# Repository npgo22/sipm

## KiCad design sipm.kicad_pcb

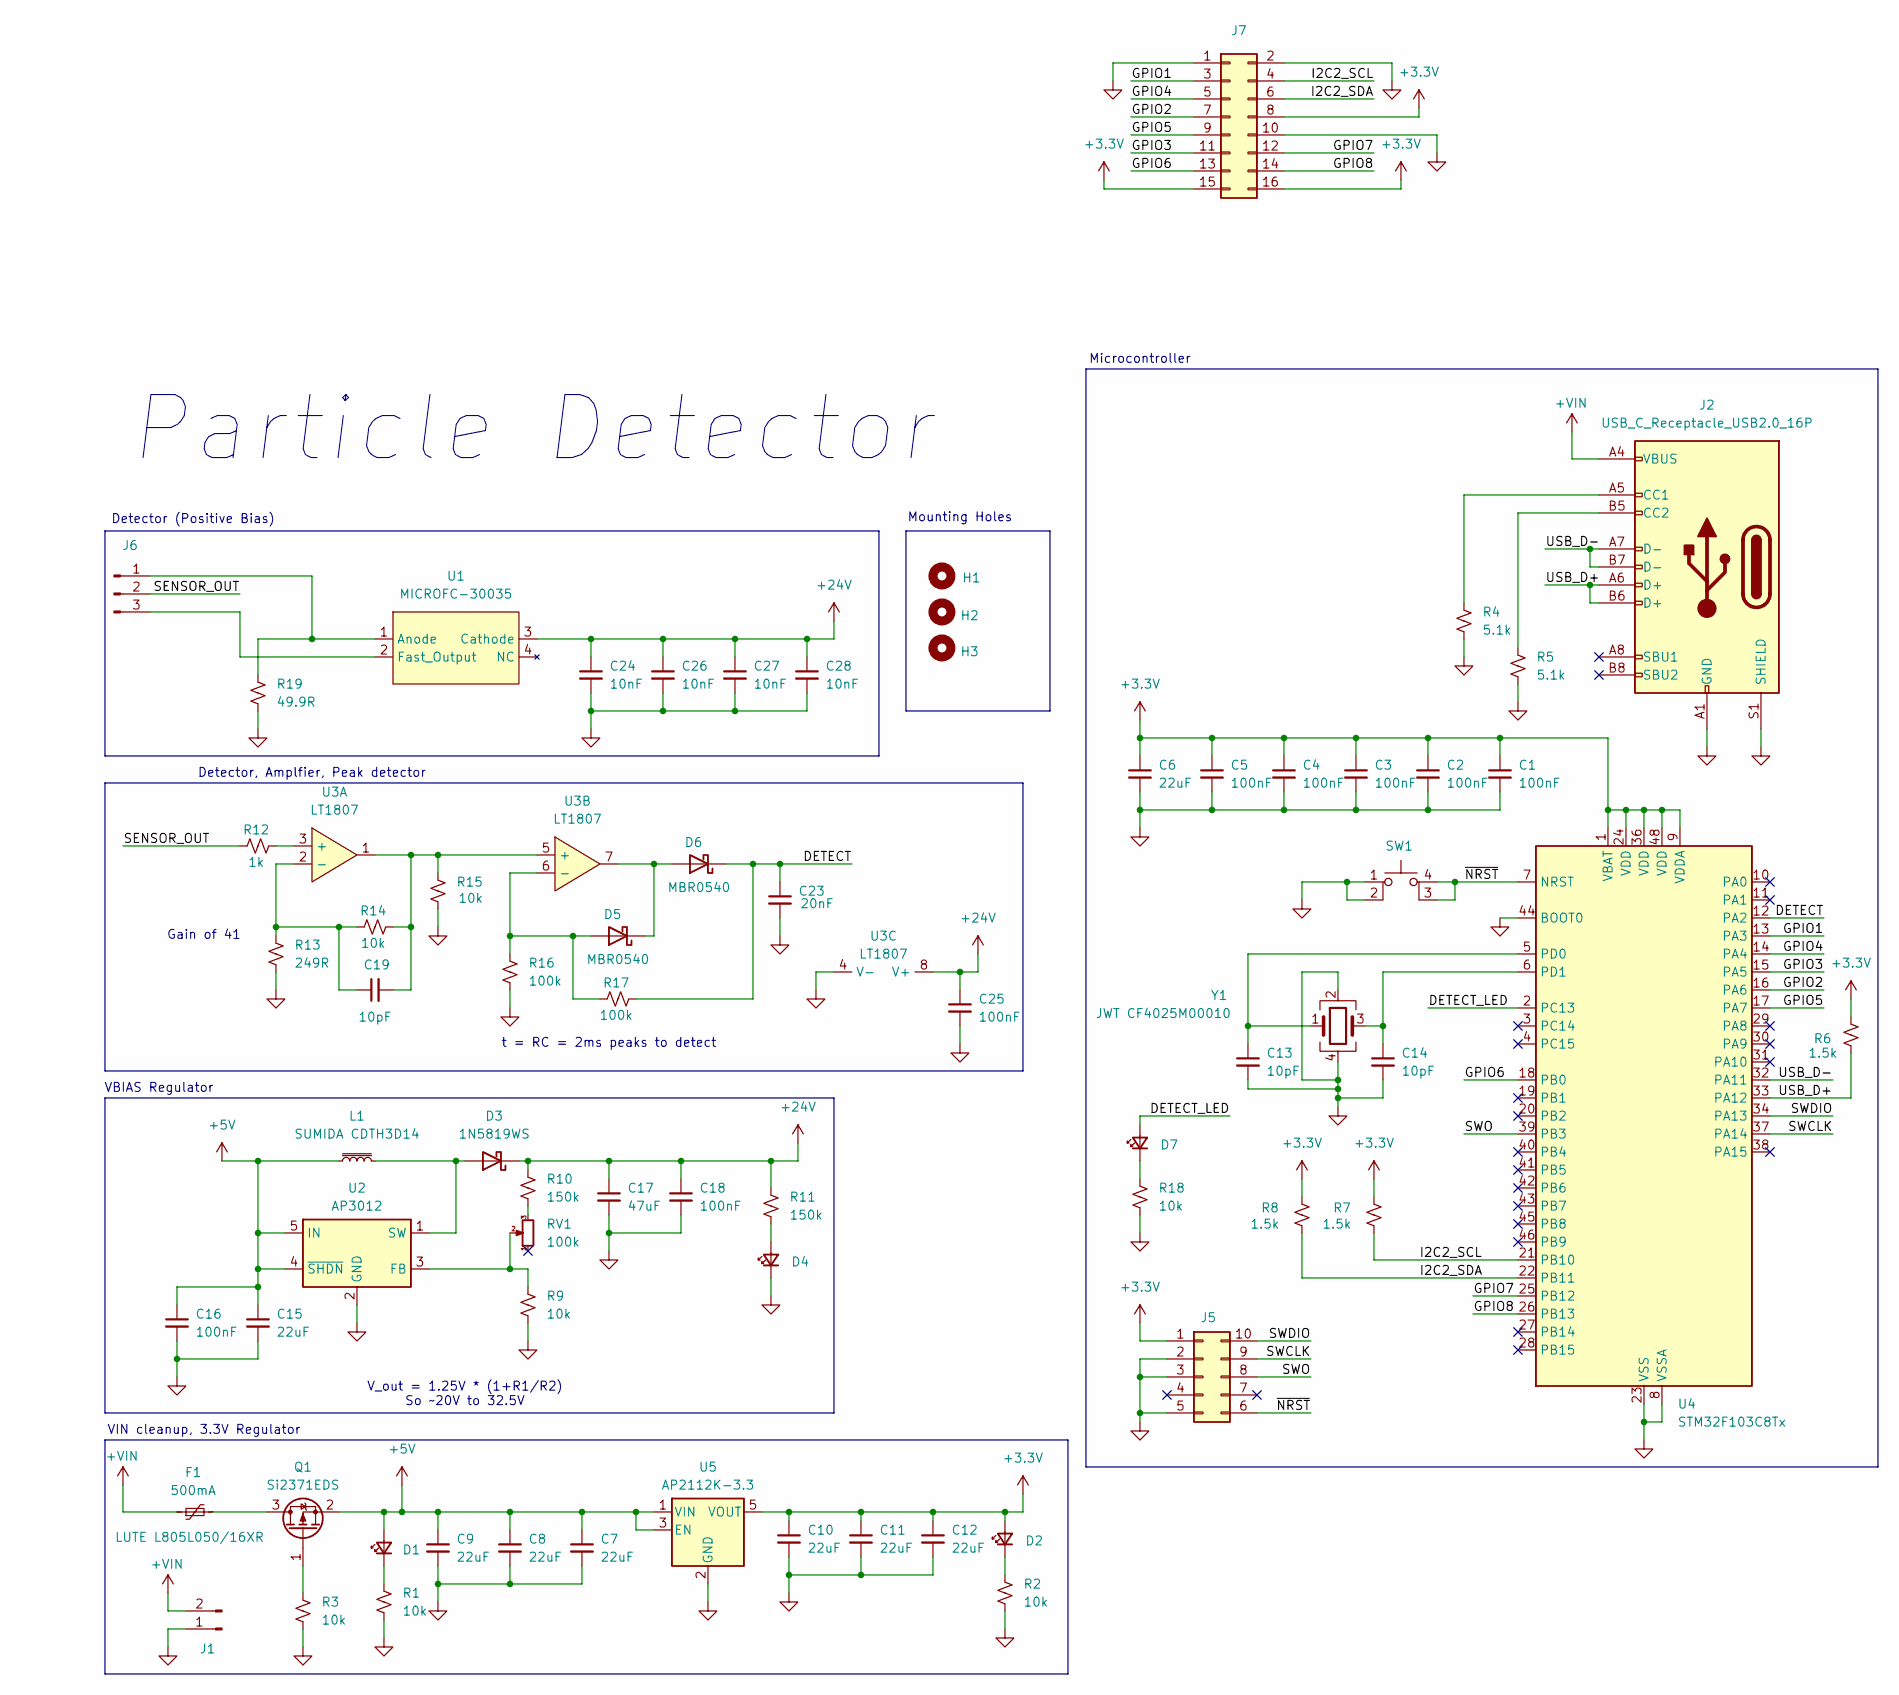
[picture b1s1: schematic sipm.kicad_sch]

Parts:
C1, C2, C3, C4, C5, C16, C18, C25: 100nF; C_0603
C6, C7, C8, C9, C10, C11, C12, C15: 22uF; C_0805
C13, C14, C19: 10pF; C_0603
C17: 47uF; CP_Elec_6.3x5.7
C23: 20nF; C_0603
C24, C26, C27, C28: 10nF; C_0603
D1, D2, D4, D7: LED_Small; LED_0603
D3: 1N5819WS; D_SOD-123F
D5, D6: MBR0540; D_SOD-123
F1: 500mA; F0805
H1, H2, H3: MountingHole; MountingHole_2.2mm_M2
J1: Conn_01x02_Pin; PinHeader_1x02_P2.54mm_Vertical_SMD_Pin1Right
J2: USB_C_Receptacle_USB2.0_16P; USB_C_Receptacle_HRO_TYPE-C-31-M-12
J5: Conn_02x05_Counter_Clockwise; PinHeader_2x05_P2.54mm_Vertical_SMD
J6: Conn_01x03_Pin; PinHeader_1x03_P2.54mm_Vertical_SMD_Pin1Right
J7: Conn_02x08_Top_Bottom; PinHeader_2x08_P2.54mm_Vertical_SMD
L1: SUMIDA CDTH3D14
Q1: Si2371EDS; SOT-23
R1, R2, R3, R9, R14, R15, R18: 10k; R_0603
R4, R5: 5.1k; R_0603
R6, R7, R8: 1.5k; R_0603
R10, R11: 150k; R_0603
R12: 1k; R_0603
R13: 249R; R_0603
R16, R17: 100k; R_0603
R19: 49.9R; R_0603
RV1: 100k; Potentiometer_Vishay_TS53YL_Vertical
SW1: SW_MEC_5E; SKRPANE010
U1: MICROFC-30035; XDCR_MICROFC-30035-SMT-TR1
U2: AP3012; SOT-23-5
U3: LT1807; SOIC-8
U4: STM32F103C8Tx; LQFP-48_7x7mm_P0.5mm
U5: AP2112K-3.3; SOT-23-5
Y1: JWT CF4025M00010; 3225-4P

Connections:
+3.3V: C1.1, C2.1, C3.1, C4.1, C5.1, C6.1, C10.1, C11.1, C12.1, D2.2 (A), J5.1, J7.8, J7.15, J7.16, R6.2, R7.2, R8.2, U4.1 (VBAT), U4.9 (VDDA), U4.24 (VDD), U4.36 (VDD), U4.48 (VDD), U5.5 (VOUT)
+5V: C7.1, C8.1, C9.1, C15.1, C16.1, D1.2 (A), L1.1, Q1.2 (S), U2.4 (~SHDN), U2.5 (IN), U5.1 (VIN), U5.3 (EN)
+24V: C17.1, C18.1, C24.1, C25.1, C26.1, C27.1, C28.1, D3.1 (K), R10.1, R11.1, U1.3 (Cathode), U3.8 (V+)
+VIN: F1.1, J1.2, J2.A4 (VBUS), J2.A9 (VBUS), J2.B4 (VBUS), J2.B9 (VBUS)
/DETECT: C23.1, D6.1 (K), R17.2, U4.12 (PA2)
/DETECT_LED: D7.2 (A), U4.2 (PC13)
/GPIO1: J7.3, U4.13 (PA3)
/GPIO2: J7.7, U4.16 (PA6)
/GPIO3: J7.11, U4.15 (PA5)
/GPIO4: J7.5, U4.14 (PA4)
/GPIO5: J7.9, U4.17 (PA7)
/GPIO6: J7.13, U4.18 (PB0)
/GPIO7: J7.12, U4.25 (PB12)
/GPIO8: J7.14, U4.26 (PB13)
/I2C2_SCL: J7.4, R7.1, U4.21 (PB10)
/I2C2_SDA: J7.6, R8.1, U4.22 (PB11)
/SENSOR_OUT: J6.2, R12.1
/SWCLK: J5.9, U4.37 (PA14)
/SWDIO: J5.10, U4.34 (PA13)
/SWO: J5.8, U4.39 (PB3)
/USB_D+: J2.A6 (D+), J2.B6 (D+), R6.1, U4.33 (PA12)
/USB_D-: J2.A7 (D-), J2.B7 (D-), U4.32 (PA11)
/~NRST: J5.6, SW1.3 (K), SW1.4 (A), U4.7 (NRST)
GND: C1.2, C2.2, C3.2, C4.2, C5.2, C6.2, C7.2, C8.2, C9.2, C10.2, C11.2, C12.2, C13.2, C14.2, C15.2, C16.2, C17.2, C18.2, C23.2, C24.2, C25.2, C26.2, C27.2, C28.2, D4.1 (K), J1.1, J2.A1 (GND), J2.A12 (GND), J2.B1 (GND), J2.B12 (GND), J2.S1 (SHIELD), J5.2, J5.3, J5.5, J7.1, J7.2, J7.10, R1.2, R2.2, R3.2, R4.2, R5.2, R9.2, R13.2, R15.2, R16.2, R18.2, R19.2, SW1.1, SW1.2, U2.2 (GND), U3.4 (V-), U4.8 (VSSA), U4.23 (VSS), U4.35 (VSS), U4.44 (BOOT0), U4.47 (VSS), U5.2 (GND), Y1.2, Y1.4
unnamed: D1.1 (K), R1.1
unnamed: D2.1 (K), R2.1
unnamed: D3.2 (A), L1.2, U2.1 (SW)
unnamed: D4.2 (A), R11.2
unnamed: D5.2 (A), R16.1, R17.1, U3.6 (-)
unnamed: D5.1 (K), D6.2 (A), U3.7
unnamed: D7.1 (K), R18.1
unnamed: J2.A5 (CC1), R4.1
unnamed: J2.B5 (CC2), R5.1
unnamed: J6.1, R19.1, U1.1 (Anode)
unnamed: J6.3, U1.2 (Fast_Output)
unnamed: F1.2, Q1.3 (D)
unnamed: Q1.1 (G), R3.1
unnamed: R10.2, RV1.3
unnamed: R9.1, RV1.2, U2.3 (FB)
unnamed: R12.2, U3.3 (+)
unnamed: C19.1, R13.1, R14.1, U3.2 (-)
unnamed: C19.2, R14.2, R15.1, U3.1, U3.5 (+)
unnamed: C13.1, U4.5 (PD0), Y1.1
unnamed: C14.1, U4.6 (PD1), Y1.3

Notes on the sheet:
Microcontroller
Gain of 41
VIN cleanup, 3.3V Regulator
Particle Detector
Detector, Amplfier, Peak detector
Detector (Positive Bias)
t = RC = 2ms peaks to detect
Mounting Holes
VBIAS Regulator
V_out = 1.25V * (1+R1/R2) So ~20V to 32.5V

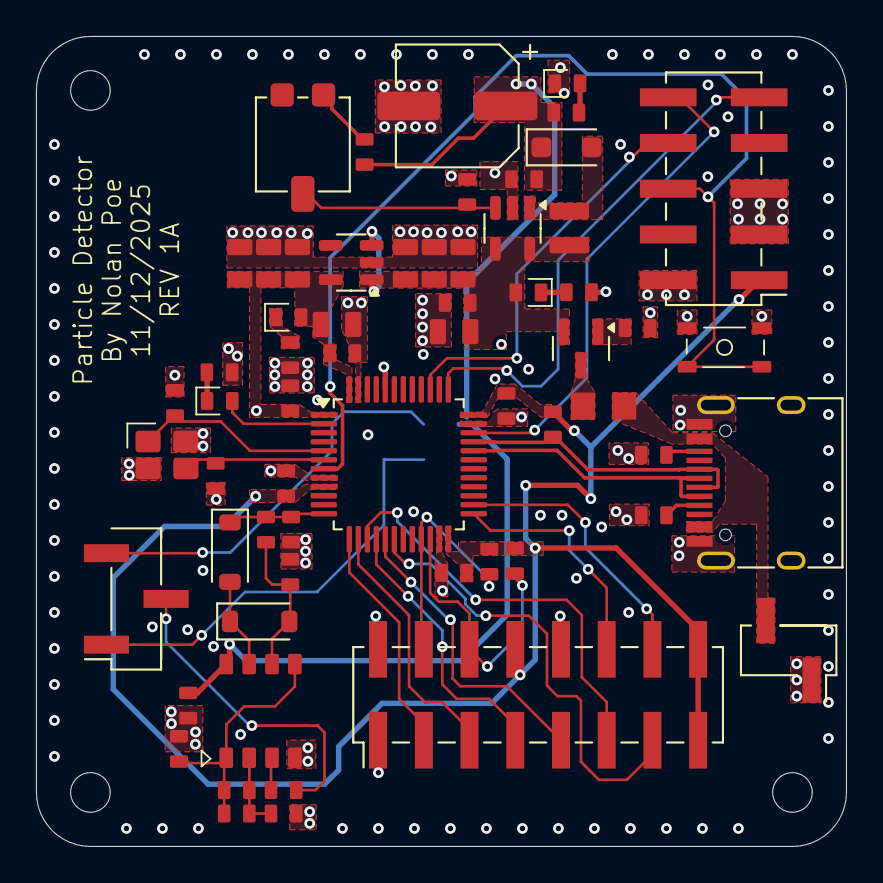
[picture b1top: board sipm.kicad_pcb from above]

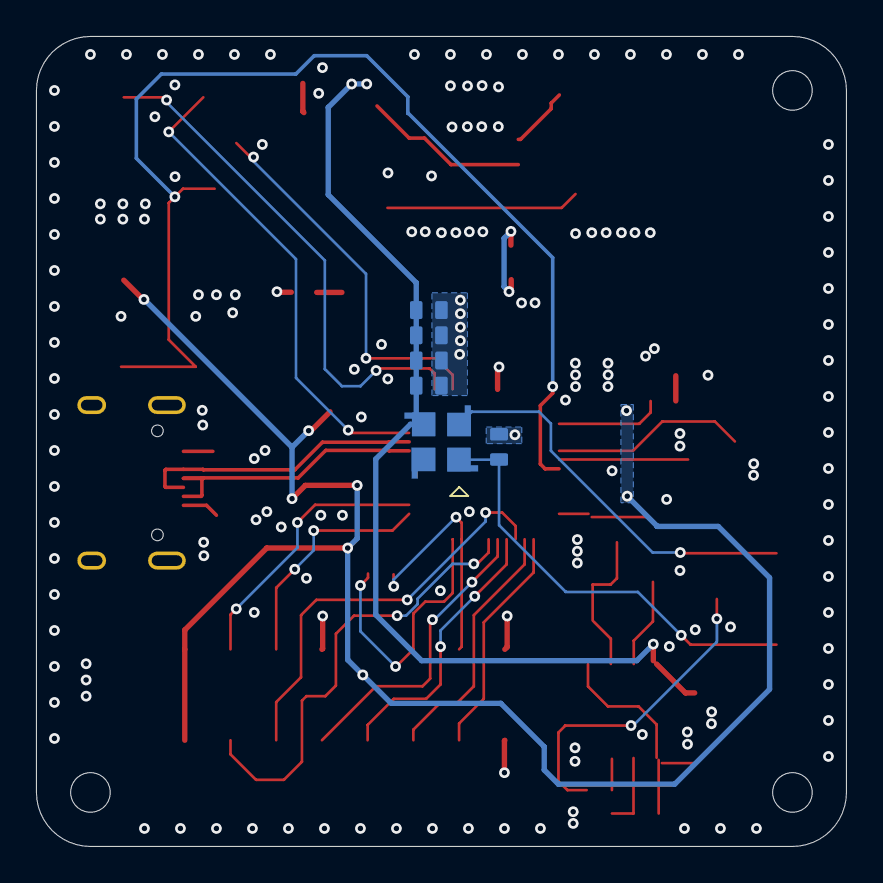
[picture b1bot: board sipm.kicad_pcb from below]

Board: 4 copper layers, 45.0 x 45.0 mm, 70 parts (6 on the bottom side), 44 nets.

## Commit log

2025-11-12 Commit empty output dir
2025-11-12 point kibot to correct config
2025-11-12 Properly set output directory
2025-11-12 Fix combined PDF path
